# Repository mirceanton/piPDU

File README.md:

# piPDU

A Raspberry Pi powered PDU for the Homelab.

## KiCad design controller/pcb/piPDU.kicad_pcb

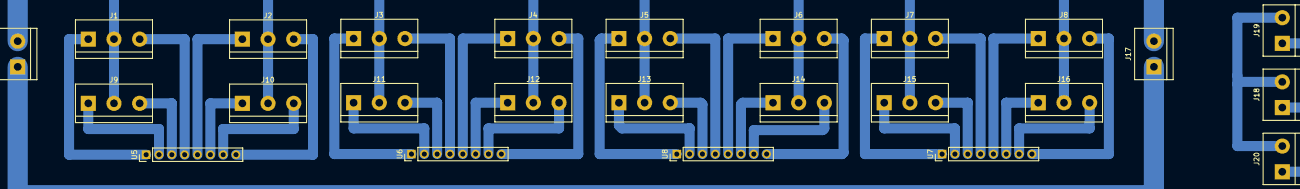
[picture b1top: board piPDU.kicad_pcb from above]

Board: 2 copper layers, 25 parts (0 on the bottom side), 36 nets.

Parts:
J0: SCR_5V1; TerminalBlock_bornier-2_P5.08mm
J1: SCR_BTN_1; TerminalBlock_bornier-3_P5.08mm
J2: SCR_BTN_2; TerminalBlock_bornier-3_P5.08mm
J3: SCR_BTN_3; TerminalBlock_bornier-3_P5.08mm
J4: SCR_BTN_4; TerminalBlock_bornier-3_P5.08mm
J5: SCR_BTN_5; TerminalBlock_bornier-3_P5.08mm
J6: SCR_BTN_6; TerminalBlock_bornier-3_P5.08mm
J7: SCR_BTN_7; TerminalBlock_bornier-3_P5.08mm
J8: SCR_BTN_8; TerminalBlock_bornier-3_P5.08mm
J9: SCR_BTN_9; TerminalBlock_bornier-3_P5.08mm
J10: SCR_BTN_10; TerminalBlock_bornier-3_P5.08mm
J11: SCR_BTN_11; TerminalBlock_bornier-3_P5.08mm
J12: SCR_BTN_12; TerminalBlock_bornier-3_P5.08mm
J13: SCR_BTN_13; TerminalBlock_bornier-3_P5.08mm
J14: SCR_BTN_14; TerminalBlock_bornier-3_P5.08mm
J15: SCR_BTN_15; TerminalBlock_bornier-3_P5.08mm
J16: SCR_BTN_16; TerminalBlock_bornier-3_P5.08mm
J17: SCR_5V2; TerminalBlock_bornier-2_P5.08mm
J18, J19, J20: SCR_i2c; TerminalBlock_bornier-2_P5.08mm
U5, U6, U7, U8: 8P_Header; PinHeader_1x08_P2.54mm_Vertical

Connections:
+5V: J0.2, J1.2, J2.2, J3.2, J4.2, J5.2, J6.2, J7.2, J8.2, J9.2, J10.2, J11.2, J12.2, J13.2, J14.2, J15.2, J16.2, J17.2
BTN1: J1.3, U5.4
BTN2: J2.3, U5.8
BTN3: J3.3, U6.4
BTN4: J4.3, U6.8
BTN5: J5.3, U8.4
BTN6: J6.3, U8.8
BTN7: J7.3, U7.4
BTN8: J8.3, U7.8
BTN9: J9.3, U5.3
BTN10: J10.3, U5.7
BTN11: J11.3, U6.3
BTN12: J12.3, U6.7
BTN13: J13.3, U8.3
BTN14: J14.3, U8.7
BTN15: J15.3, U7.3
BTN16: J16.3, U7.7
GND: J0.1, J17.1
LED1: J1.1, U5.1
LED2: J2.1, U5.5
LED3: J3.1, U6.1
LED4: J4.1, U6.5
LED5: J5.1, U8.1
LED6: J6.1, U8.5
LED7: J7.1, U7.1
LED8: J8.1, U7.5
LED9: J9.1, U5.2
LED10: J10.1, U5.6
LED11: J11.1, U6.2
LED12: J12.1, U6.6
LED13: J13.1, U8.2
LED14: J14.1, U8.6
LED15: J15.1, U7.2
LED16: J16.1, U7.6
SCL: J18.1, J19.1, J20.1
SDA: J18.2, J19.2, J20.2

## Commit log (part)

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2022-12-04 Implement config singleton.
2022-12-04 Add sample config file
2022-12-04 Implement singleton class to handle communication with arduino
2022-12-04 Add doc comments and make sure the singletons are always initialized
2022-12-04 Create a basic flask API server
2022-12-04 Add API endpoint to toggle sockets on/off
2022-12-04 Cache the socket states in an array
2022-12-04 Add method to send data over serial
2022-12-04 Return jsonified payloads and add route to check status for a given socket
2022-12-04 Export metrics received from serial via prometheus exporter
2022-12-04 Print the data string, not the array
2022-12-04 Rename `raspberry.py` -> `server.py`
2022-12-04 Add pip requirements file for the server
2022-12-04 Move files
2022-12-04 Initialize mkdocs-material docs
2022-12-04 Update docs.
2022-12-04 Fix.
2022-12-07 Move utility classes to a dedicated directory
2022-12-07 Initialize controller code
2022-12-08 Fix imports
2022-12-08 Add support for the LCD screen
2022-12-08 Move individual pieces of code to dedicated directories
2022-12-08 Add KiCAD PCB Design
2022-12-11 Create the config singleton
2022-12-11 Create requirements file
2022-12-11 Create LCD singleton
2022-12-11 clean up main code
2022-12-11 Change pins from BOARD to BCM notation
2022-12-11 Initialize LEDs
2022-12-11 Scrape pipdu server prometheus metrics endpoint
2022-12-11 Ensure GPIOs are cleaned up at the end
2022-12-11 [WIP] Initialize button array and configure interrupts
2022-12-13 Extract code to arduino-style functions
2022-12-13 Implement singleton class to handle buttons short and long presses in the matrix
2022-12-13 Update defaults
2022-12-13 Implement metrics singleton to handle storing and collecting metrics
2022-12-13 Create LED functions
2022-12-13 Cleanup
2022-12-13 Refactor using new classes
2022-12-15 Implement led_array_update
2022-12-15 Implement LCD States enum, setState method, update method, idle and info states
2022-12-15 Change indentation to spaces. Implement short and long press
2022-12-20 Update gitignore to ignore kicad backups
2022-12-20 Remove previous kicad backup
2022-12-20 Remove redundant connections from the schematic
2022-12-20 Fix PCB and schematic redundant connections
2022-12-20 Add board outline
2022-12-20 Add mounting holes to PCB
2022-12-20 Save project
2022-12-23 Move the api routes to dedicated files in the `routes/` directory
2022-12-23 Define all required routes
2022-12-23 Move the api routes to a dedicated directory and organize them based on version. Implement the /socket and /sockets endpoints with all the required functions
2022-12-23 add dedicated commands for turn on and turn off instead of just toggle
2022-12-23 Parse the socket config file && Add socket config sample
2022-12-23 Uncomment metrics thread.
2022-12-24 MAJOR refactoring and cleanup... with minimal testing... Godspeed to future me
2022-12-24 Rename file
2022-12-24 Add socket toggle endpoint
2022-12-24 Add socket toggle functionality
2022-12-24 Switch to named import
2022-12-24 Fix broken URL
2022-12-24 Fix function name
2022-12-24 Implement Led class and LedArray Singleton
2022-12-24 Use the newly created utility classes
2022-12-24 Add functionality to trigger pre and post event hooks
2023-01-02 Remove gerber files
2023-01-02 Make tracks thicker and more spaced out
2023-01-03 Add Circuit Schematic for the Server
2023-01-05 Update controller PCB and schematic to use GPIO expanders
2023-01-05 Update server schematic to use the Arduino Mega as I2C expander and remove the PCB design
2023-01-24 Cleanup for separate feature branches.
2023-01-24 Update the code to handle the buttons and LEDS via PCF8574 expanders
2023-02-05 Restructure project.
2023-02-05 Rename sketch to match folder name
2023-02-05 Include library directly
2023-02-05 Fix indentation
2023-02-05 Add the ACS712 Library
2023-02-05 Add notice of the original author
2023-02-06 Remove library
2023-02-06 Implement custom functionality
2023-02-06 Migrate to the new libraries.
2023-02-06 Reset values at the end of the calculation.
2023-02-06 Add ability to get raw analogRead data
2023-02-06 Implement noise floor
2023-02-06 Rename getCurrent() -> getAmps()
2023-02-06 Implement `getWatts()` assuming 230V source
2023-02-06 Update with new functionalities
2023-02-06 Cleanup serial output.
2023-02-06 Add trailing newline
2023-02-06 [Server] Create PCB Schematic (#15)
    * Implement config singleton.
    * Add sample config file
    * Implement singleton class to handle communication with arduino
    * Add doc comments and make sure the singletons are always initialized
    * Create a basic flask API server
    * Add API endpoint to toggle sockets on/off
2023-02-06 [Controller] Add PCB and Circuit Schematics (#14)
    * Implement config singleton.
    * Add sample config file
    * Implement singleton class to handle communication with arduino
    * Add doc comments and make sure the singletons are always initialized
    * Create a basic flask API server
    * Add API endpoint to toggle sockets on/off
2023-02-06 Implement communication over i2c.
2023-02-06 Rename function
2023-02-06 Refactor 'handleMessage'
2023-02-06 Add debug messages to usb serial
2023-02-06 Set device address.
2023-02-15 fix: Move `return` and `print` outside the for loop
2023-02-15 Add top-level if guard in handleMessage function
2023-02-15 Refactor multiple print statements into single-line
2023-02-15 Rename variable + make it a constant
2023-02-15 Remove redundant comments
2023-02-15 Mark variable as const
2023-02-15 Implement `onRequest` handler
2023-02-15 Add more "debug" print statements.
2023-02-15 Create a makefile
2023-02-16 Serial Router Microservice: Initial Implementation
2023-02-16 Metrics Scheduler Microservice: Initial Implementation
2023-02-16 Metrics Server Microservice: Initial Implementation
2023-02-17 Refactor the code
2023-02-17 Remove file
2023-02-17 Create the requirements file for the metrics-scheduler
2023-02-17 Create the dockerfile for the metrics-scheduler
2023-02-17 Refactor code.
2023-02-17 Refactor and add logging statements
2023-02-17 Add more logging
2023-02-17 Create the basic structure for the api server.
2023-02-17 Generate requirements file
2023-02-18 Create RabbitMQ Helper for API v1
2023-02-18 Add socket helper for API v1
2023-02-18 Implement paths using helpers
2023-02-18 Update the code with individual on/off commands
2023-02-18 Improve command parser
2023-02-18 Update Dockerfile
2023-02-18 Create dockerfile to upload arduino code
2023-02-18 Exit if rabbitmq is not available
2023-02-18 Create the docker-compose file for dev/testing
2023-02-18 Purge the old code
2023-02-19 Refactor into dedicated files per scope
2023-02-19 Refactor
2023-02-19 Add requirements file
2023-02-20 Increase the baud rate
2023-02-20 Flush the serial buffer
2023-02-20 Set the baud rate for debugging
2023-02-20 Fix '`cmd` not found' error
2023-02-20 Add `before_request` validator for socket id
2023-02-20 Fix dockerfile
2023-02-21 Remove redundant flush of input buffer during output writes
2023-02-21 Reset buffers when initializing the device
2023-02-21 Make sure the output buffer is emptied and the message sent
2023-02-21 Refactor rabbitmq callback
2023-02-21 Exit in case of error and let the docker container restart
2023-02-21 Add "debug" print statements
2023-02-21 Extract connection params as params to constructor
2023-02-21 Extract the rabbitmq connection details as constructor params
2023-02-21 Make all vars configurable and set defaults for some
2023-02-21 Run python with unbuffered output
2023-02-21 Update state cache when requesting state change
2023-02-21 Fix `connection reset by peer` error
2023-02-23 Refactor to non-blocking rabbitmq consume
2023-02-23 Remove service that is no longer needed
2023-02-23 Update message syntax
2023-02-23 Update message syntax + remove useless utility
2023-02-23 Update compose file
2023-02-24 [Server] Implement Functionality
2023-02-24 [Server] Initial Implementation.
2023-02-24 Include sub-pipeline
2023-02-24 Create separate build jobs for release and dev
2023-02-24 Update pipeline && Add version file
2023-02-24 Remove docker command
2023-02-24 Test
2023-02-24 Fix?
2023-02-24 Rename steps and cleanup
2023-02-24 Add more comments
2023-02-24 Try splitting the pipelines
2023-02-28 Add TODO Comments
2023-02-28 Refactor && Fix
2023-02-28 Add pipdu server addr constant
2023-02-28 Create socket api helper
2023-02-28 Add missing import
2023-02-28 Fix array type
2023-02-28 Try fix?
2023-02-28 Undo
2023-02-28 Fix var name
2023-02-28 Add requirements
2023-02-28 Create a sample dockerfile
2023-03-01 Initialize new service
2023-03-01 Create dummy test
2023-03-01 Initial implementation
2023-03-01 Create dockerfile
2023-03-01 Create basic structure
2023-03-03 proof-of-concept
2023-03-06 Refactor and implement named pipes && display state timeout
2023-03-06 Add missing env var
2023-03-06 Cleanup old code
2023-03-06 remove unused file
2023-03-06 Create a sample docker-compose file
2023-03-06 Try a pipeline?
2023-03-06 try fix
2023-03-06 Install libffi-dev
2023-03-06 Fix linting
2023-03-06 Separate dev and prod requirements
2023-03-06 Update pipeline
2023-03-06 Split build into parallel steps
2023-03-06 Add more CI
2023-03-06 Fix invalid docker tag name
2023-03-06 Rename jobs so they are not the same name
2023-03-06 Fix linting errors
2023-03-06 Add missing dummy test
2023-03-06 Install missing prereqs
2023-03-06 Fix global variables overriding each other.
2023-03-07 Add rules to only run the pipelines if changes were made to the associated files.
2023-03-07 Imeplemt CI template
2023-03-07 Try templating using `extends`
2023-03-07 Try fix.
2023-03-07 [Controller] Implement Functionality
2023-03-07 [Controller] Initial Implementation
2023-03-07 Fix release pipeline
2023-03-07 Fix linting issues.
2023-03-07 Add missing version
2023-03-07 Migrate to debian base image
2023-03-07 Add caching && Fix formatting
2023-03-07 Fix pipeline
2023-03-07 Add the `-y` flag to `apt install`
2023-03-07 Implement `before_script` as per the gitlab-ci doc example
2023-03-07 Add some issue templates
2023-03-07 Create a generic MR template
2023-03-07 Remove `build:` statements
2023-03-07 Fix CI
2023-04-01 Fix typo
2023-04-01 Init "subrepo"
2023-04-01 Create structure
2023-04-01 Implement `testConnection`
2023-04-01 Implement `setStateFor`
2023-04-01 Implement `getStateFor`
2023-04-01 Implement metrics scraping
2023-04-01 Add support for SSL
2023-04-01 Add README
2023-04-01 Add setup scripts
2023-04-01 Add pipeline to publish the package
2023-04-01 Rename package directory
2023-04-01 Update versioning logic
2023-04-01 Fix path
2023-04-01 Fix package
2023-04-01 Fix lint
2023-04-01 Fix job order
2023-04-01 Add dummy test
2023-04-01 Remove tests
2023-04-01 Remove unused include
2023-04-01 Fix includes
2023-04-01 Rename job
2023-04-03 Implement client config parsing
2023-04-03 Move the PiPDU class to a dedicated file
2023-04-03 Import all required utils
2023-04-03 DEBUG: print pip version
2023-04-03 DEBUG
2023-04-03 Fix lint stage and add tests stage
2023-04-03 Update ALL CI
2023-04-03 Fix job name
2023-04-03 Add version suffix for pip
2023-04-04 Fix URL
2023-04-04 hardcode the version
2023-04-04 Try hardcoded version
2023-04-04 Use sed to hardcode the package version
2023-04-04 Update VERSION_SUFFIX to be unique across builds
2023-04-04 Try to rename the source code dir
2023-04-04 Lint everything
2023-04-04 Retry fix
2023-04-04 Simplify syntax check
2023-04-04 Fix mismatch type
2023-04-06 Update setup
2023-04-06 Restructure
2023-04-06 Update key comparison
2023-04-06 Fix package name
2023-04-06 Add support for missing required keys
2023-04-06 Make the `name` key optional
2023-04-06 Fix included packages
2023-04-06 First working prototype
2023-04-06 Implement pip-package structure
2023-04-11 Migrate from rabbitmq to named pipe
2023-04-11 Migrate to named pipe
2023-04-11 remove unused dependency
2023-04-11 Make sure the pipe is created
2023-04-11 Major refactoring
2023-04-11 Ignore GPIO warnings
2023-04-11 Refactor into dedicated files
2023-04-11 Define some tests
2023-04-11 Update the dockerfile
2023-04-11 Add some documentation
2023-04-11 Remove unused service
2023-04-11 Update config file structure
2023-04-11 Add some docs
